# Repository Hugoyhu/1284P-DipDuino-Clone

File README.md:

# 1284P-DipDuino-Clone
Small form factor 1284P Development Board inspired by AtomSoftTech's DipDuino(https://www.tindie.com/products/atomsoft/dipduino-12/).

Schematic was based off Dcelectr's 1284P Schematic(https://github.com/dcelectr/ATmega1284P_Board), and USB bridge schematic from Sparkfun(https://www.sparkfun.com/products/15096)

Designed with KiCAD EDA.

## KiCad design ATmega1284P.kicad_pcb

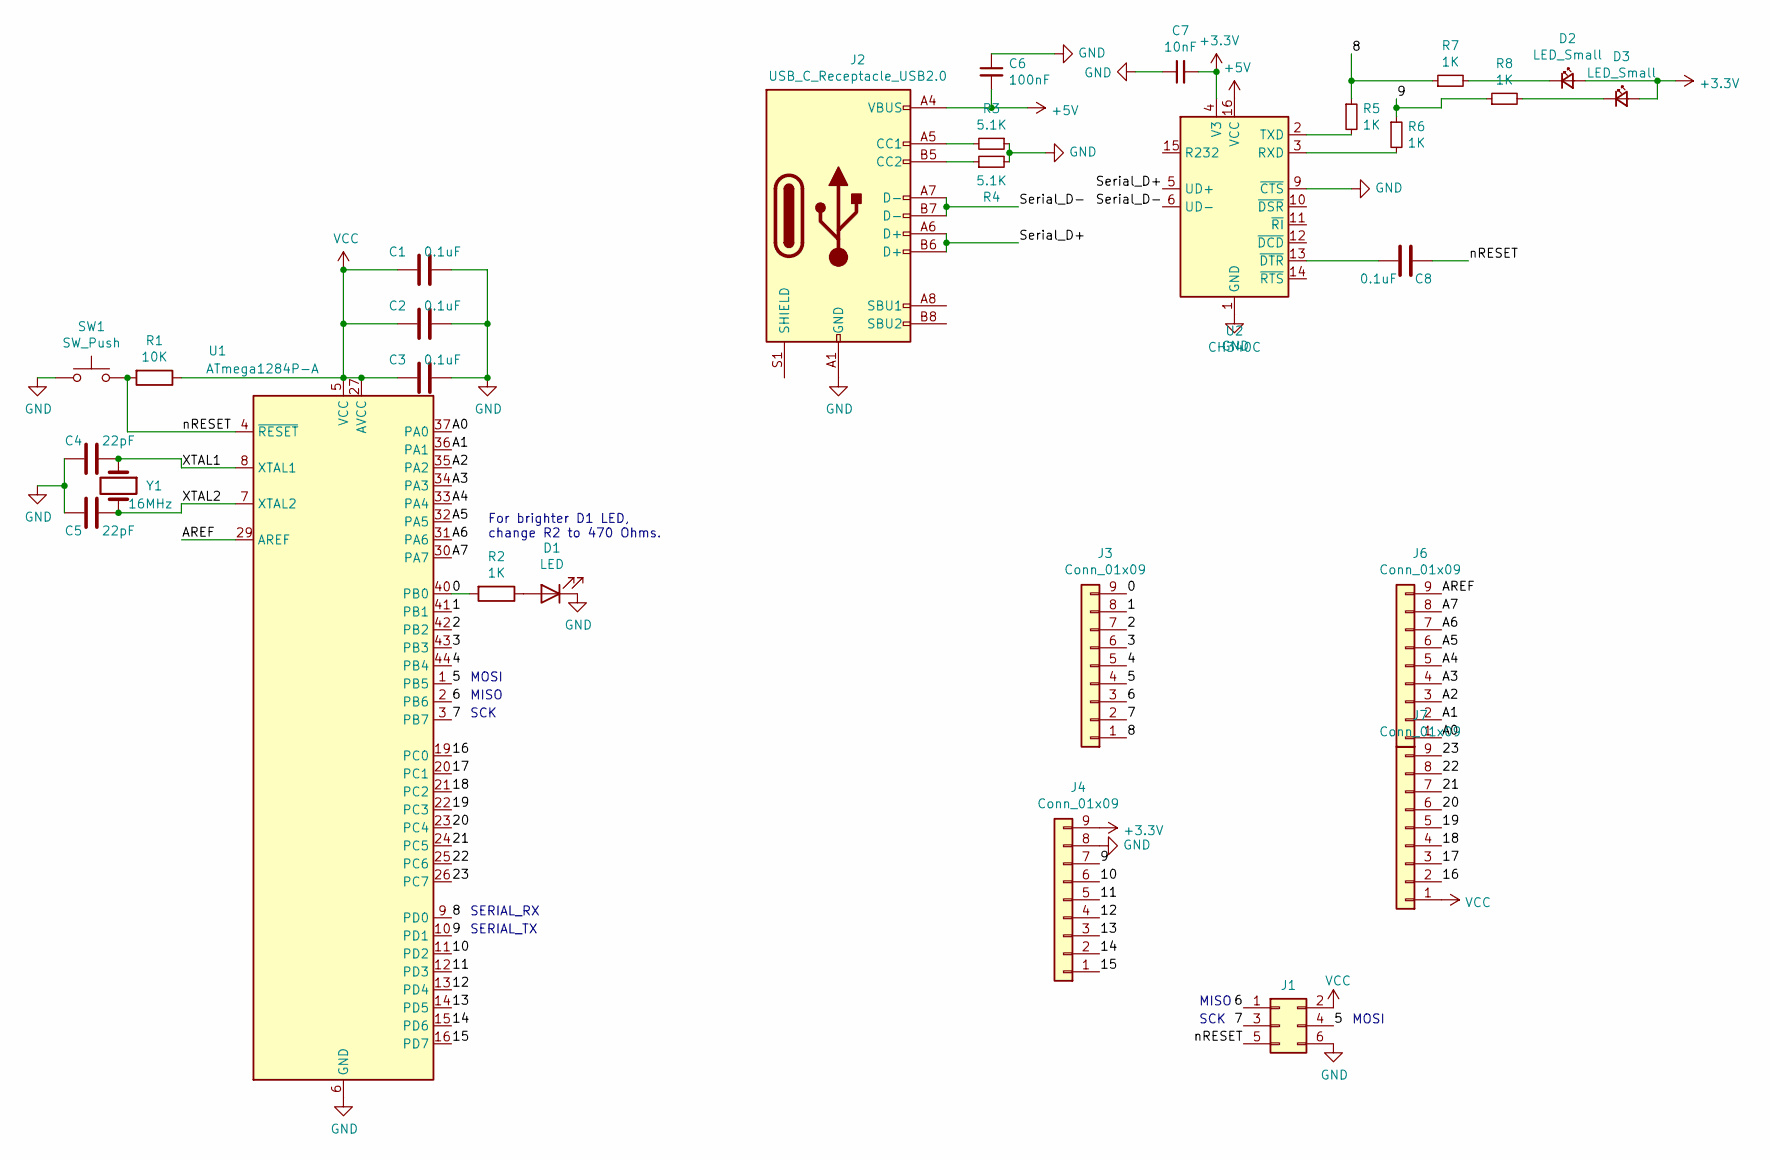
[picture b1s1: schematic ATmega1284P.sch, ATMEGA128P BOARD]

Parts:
C1, C2, C3, C8: 0.1uF; C_0805_2012Metric_Pad1.18x1.45mm_HandSolder
C4, C5: 22pF; C_0805_2012Metric_Pad1.18x1.45mm_HandSolder
C6: 100nF; C_0805_2012Metric_Pad1.18x1.45mm_HandSolder
C7: 10nF; C_0805_2012Metric_Pad1.18x1.45mm_HandSolder
D1: LED; LED_0805_2012Metric_Pad1.15x1.40mm_HandSolder
D2, D3: LED_Small; LED_0805_2012Metric_Pad1.15x1.40mm_HandSolder
J1: Conn_02x03_Odd_Even; PinHeader_2x03_P2.54mm_Vertical
J2: USB_C_Receptacle_USB2.0; GCT_USB4085-GF-A_REVA
J3, J4, J6, J7: Conn_01x09; PinSocket_1x09_P2.54mm_Vertical
R1: 10K; R_0805_2012Metric_Pad1.20x1.40mm_HandSolder
R2: 1K; R_0805_2012Metric_Pad1.20x1.40mm_HandSolder
R3, R4: 5.1K; R_0805_2012Metric_Pad1.20x1.40mm_HandSolder
R5, R6, R7, R8: 1K; R_0603_1608Metric_Pad0.98x0.95mm_HandSolder
SW1: SW_Push; SW_SPST_B3U-1000P
U1: ATmega1284P-A; TQFP-44_10x10mm_P0.8mm
U2: CH340C; SOIC-16_3.9x9.9mm_P1.27mm
Y1: 16MHz; Crystal_SMD_5032-2Pin_5.0x3.2mm_HandSoldering

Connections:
+3V3: C7.2, D2.2 (A), D3.2 (A), J4.9, U2.4 (V3)
+5V: C6.2, J2.A4 (VBUS), J2.A9 (VBUS), J2.B4 (VBUS), J2.B9 (VBUS), U2.16 (VCC)
/0: J3.9, R2.2, U1.40 (PB0)
/1: J3.8, U1.41 (PB1)
/2: J3.7, U1.42 (PB2)
/3: J3.6, U1.43 (PB3)
/4: J3.5, U1.44 (PB4)
/5: J1.4, J3.4, U1.1 (PB5)
/6: J1.1, J3.3, U1.2 (PB6)
/7: J1.3, J3.2, U1.3 (PB7)
/8: J3.1, R5.1, R7.1, U1.9 (PD0)
/9: J4.7, R6.1, R8.1, U1.10 (PD1)
/10: J4.6, U1.11 (PD2)
/11: J4.5, U1.12 (PD3)
/12: J4.4, U1.13 (PD4)
/13: J4.3, U1.14 (PD5)
/14: J4.2, U1.15 (PD6)
/15: J4.1, U1.16 (PD7)
/16: J7.2, U1.19 (PC0)
/17: J7.3, U1.20 (PC1)
/18: J7.4, U1.21 (PC2)
/19: J7.5, U1.22 (PC3)
/20: J7.6, U1.23 (PC4)
/21: J7.7, U1.24 (PC5)
/22: J7.8, U1.25 (PC6)
/23: J7.9, U1.26 (PC7)
/A0: J6.1, U1.37 (PA0)
/A1: J6.2, U1.36 (PA1)
/A2: J6.3, U1.35 (PA2)
/A3: J6.4, U1.34 (PA3)
/A4: J6.5, U1.33 (PA4)
/A5: J6.6, U1.32 (PA5)
/A6: J6.7, U1.31 (PA6)
/A7: J6.8, U1.30 (PA7)
/AREF: J6.9, U1.29 (AREF)
/Serial_D+: J2.A6 (D+), J2.B6 (D+), U2.5 (UD+)
/Serial_D-: J2.A7 (D-), J2.B7 (D-), U2.6 (UD-)
/XTAL1: C4.1, U1.8 (XTAL1), Y1.1
/XTAL2: C5.1, U1.7 (XTAL2), Y1.2
/nRESET: C8.2, J1.5, R1.2, SW1.2, U1.4 (~RESET)
GND: C1.1, C2.1, C3.1, C4.2, C5.2, C6.1, C7.1, D1.1 (K), J1.6, J2.A1 (GND), J2.A12 (GND), J2.B1 (GND), J2.B12 (GND), J4.8, R3.1, R4.2, SW1.1, U1.6 (GND), U1.18 (GND), U1.28 (GND), U1.39 (GND), U2.1 (GND), U2.9 (~CTS)
unnamed: C8.1, U2.13 (~DTR)
unnamed: D1.2 (A), R2.1
unnamed: D2.1 (K), R7.2
unnamed: D3.1 (K), R8.2
unnamed: J2.A5 (CC1), R3.2
unnamed: J2.B5 (CC2), R4.1
unnamed: R5.2, U2.2 (TXD)
unnamed: R6.2, U2.3 (RXD)
VCC: C1.2, C2.2, C3.2, J1.2, J7.1, R1.1, U1.5 (VCC), U1.17 (VCC), U1.27 (AVCC), U1.38 (VCC)

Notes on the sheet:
MOSI
MISO
SCK
SERIAL_RX
SERIAL_TX
For brighter D1 LED, change R2 to 470 Ohms.

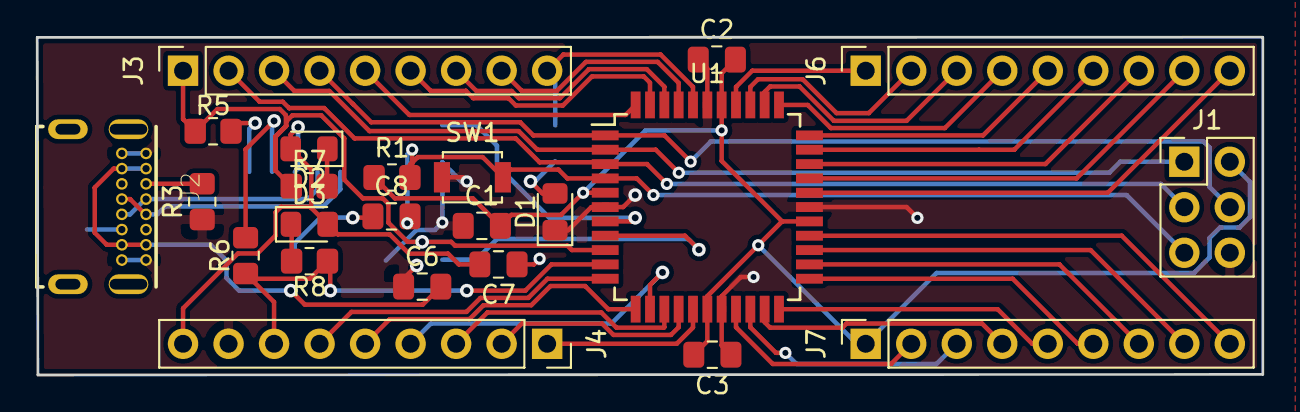
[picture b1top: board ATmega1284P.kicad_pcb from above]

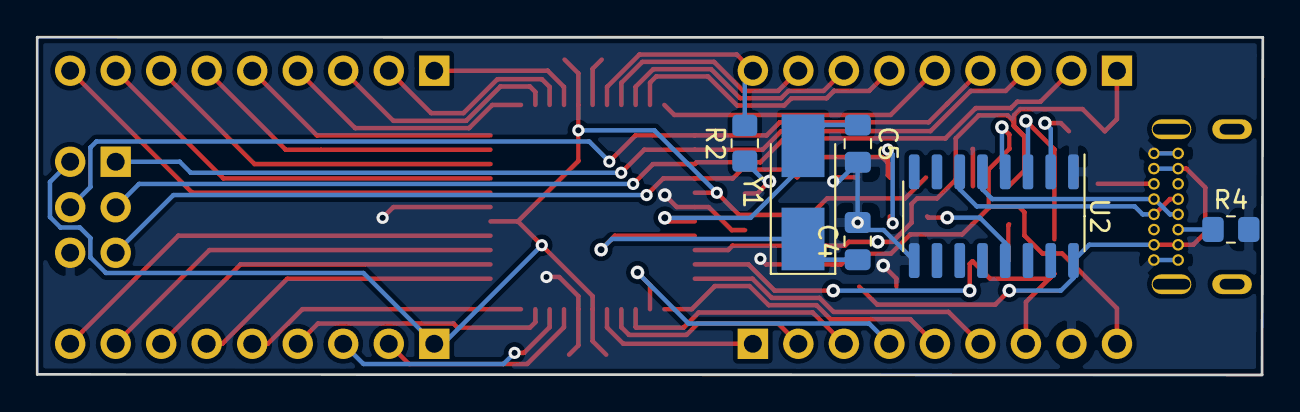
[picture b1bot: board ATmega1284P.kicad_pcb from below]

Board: 2 copper layers, 68.4 x 18.9 mm, 29 parts (6 on the bottom side), 50 nets.
